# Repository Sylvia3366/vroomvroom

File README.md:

# vroomvroom.pcb
This is a top class, 2-key macropad because 1 F1-themed macropad was not enough so I made another one. This one is a lot less cool with only 2 mechanical keys, no display screen, but you get cool LEDs :)!!

The PCB is paired with a very long description of the RB19 and many sparks and F1 symbols because why not!!! You can use this to improve your workflow by 15% since there 2 EXTRA KEYSSS.

I was inspired to make this because I love F1 and Fallout merch okay bye!!

# Schematics!

# PCB!

# BOM
| ITEM | QTY | PRICE | TOTAL | MOQ | MOQ PRICE | SOURCE |
| :--- | :---: | ---: | ---: | ---: | ---: | :--- |
| Diodes | 2 | 0.01 | 0.02 | 50 | 0.47 | https://www.lcsc.com/product-detail/C402212.html |
| LEDs | 2 | 0.08 | 0.17 | 5 | 0.44 | https://www.lcsc.com/product-detail/C5149201.html |
| Switches | 2 | 0.36 | 0.71 | 4 | 1.43 | https://e.tb.cn/h.RvXptMSPXMhfwoD?tk=n6wmgPT4OpN |
| XIAO RP2040 | 1 | 3.86 | 3.86 | 1 | 3.86 | https://e.tb.cn/h.RFUvdsQYNCUgFp4?tk=7Ln0gPTUYWn |
| M2 Screws | 2 | 0.01 | 0.01 | 100 | 0.71 | https://e.tb.cn/h.RFUDhnonnkXZCIJ?tk=oKFJgPT65Us |
| **Total** | **9** | **-** | **4.77** | **-** | **6.91** | **-** |

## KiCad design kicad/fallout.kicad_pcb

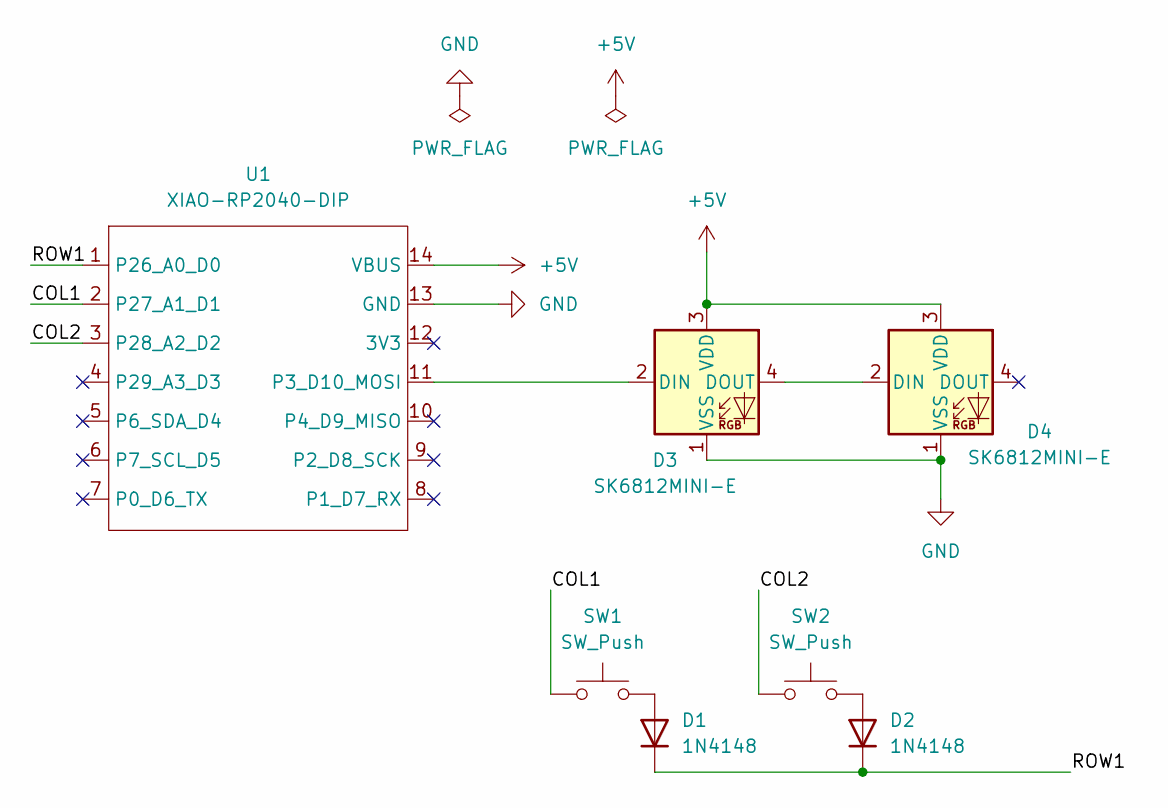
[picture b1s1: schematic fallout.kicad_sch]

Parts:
D1, D2: 1N4148; D_DO-35_SOD27_P7.62mm_Horizontal
D3, D4: SK6812MINI-E; LED_SK6812MINI-E_3.2x2.8mm_P1.5mm_ReverseMount
SW1, SW2: SW_Push; SW_Cherry_MX_1.00u_PCB
U1: XIAO-RP2040-DIP

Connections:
+5V: D3.3 (VDD), D4.3 (VDD), U1.14 (VBUS)
/COL1: SW1.1, U1.2 (P27_A1_D1)
/COL2: SW2.1, U1.3 (P28_A2_D2)
/ROW1: D1.1 (K), D2.1 (K), U1.1 (P26_A0_D0)
GND: D3.1 (VSS), D4.1 (VSS), U1.13 (GND)
unnamed: D1.2 (A), SW1.2
unnamed: D2.2 (A), SW2.2
unnamed: D3.2 (DIN), U1.11 (P3_D10_MOSI)
unnamed: D3.4 (DOUT), D4.2 (DIN)

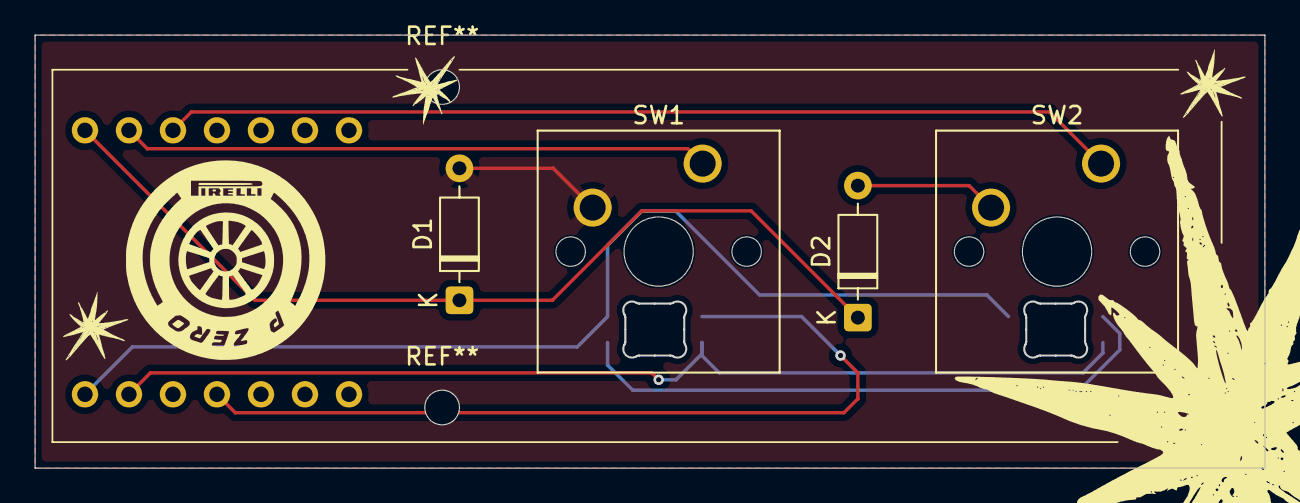
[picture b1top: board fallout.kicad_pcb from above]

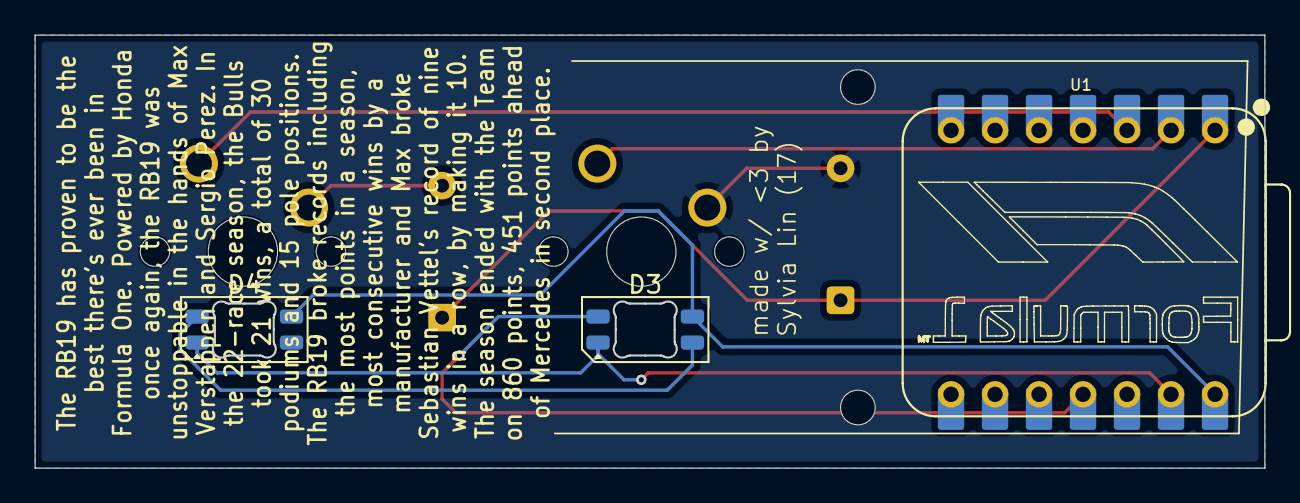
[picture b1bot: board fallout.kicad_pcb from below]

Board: 2 copper layers, 71.0 x 25.0 mm, 7 parts (3 on the bottom side), 9 nets.
